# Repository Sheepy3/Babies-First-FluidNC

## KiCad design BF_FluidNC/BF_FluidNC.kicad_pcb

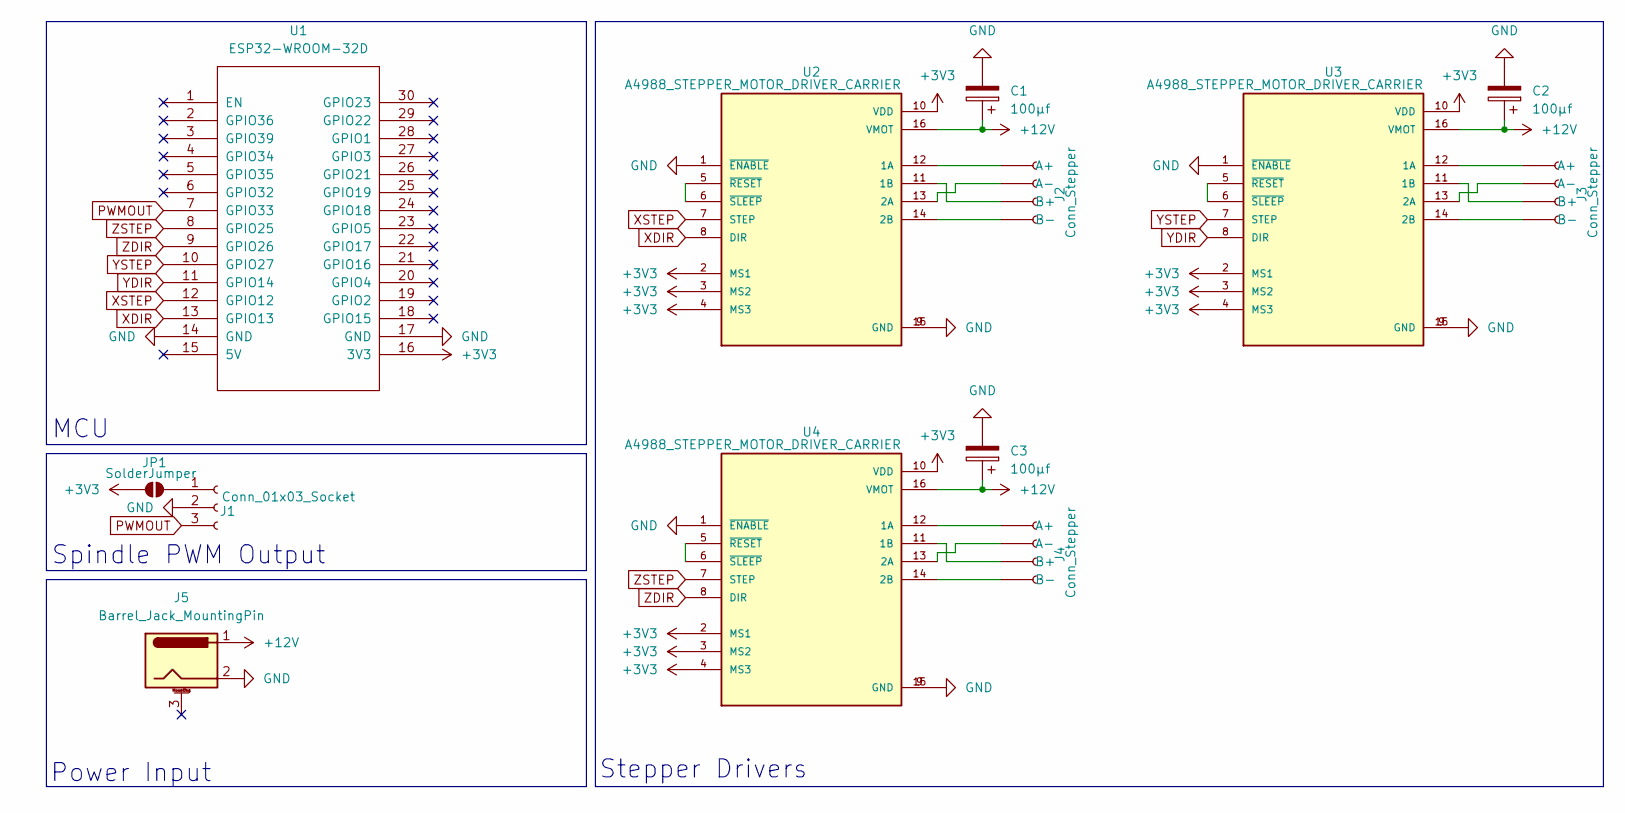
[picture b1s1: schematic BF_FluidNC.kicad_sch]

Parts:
C1, C2, C3: 100µf; CP_Radial_D5.0mm_P2.00mm
J1: Conn_01x03_Socket; PinSocket_1x03_P2.54mm_Vertical
J2, J3, J4: Conn_Stepper; PinSocket_1x04_P2.54mm_Vertical
J5: Barrel_Jack_MountingPin; BarrelJack_GCT_DCJ200-10-A_Horizontal
JP1: SolderJumper; SolderJumper-2_P1.3mm_Open_TrianglePad1.0x1.5mm
U1: ESP32-WROOM-32D; ESP32-WROOMD-Devboard
U2, U3, U4: A4988_STEPPER_MOTOR_DRIVER_CARRIER; MODULE_A4988_STEPPER_MOTOR_DRIVER_CARRIER

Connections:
+3V3: JP1.1 (A), U1.16 (3V3), U2.2 (MS1), U2.3 (MS2), U2.4 (MS3), U2.10 (VDD), U3.2 (MS1), U3.3 (MS2), U3.4 (MS3), U3.10 (VDD), U4.2 (MS1), U4.3 (MS2), U4.4 (MS3), U4.10 (VDD)
+12V: C1.1, C2.1, C3.1, J5.1, U2.16 (VMOT), U3.16 (VMOT), U4.16 (VMOT)
GND: C1.2, C2.2, C3.2, J1.2, J5.2, U1.14 (GND), U1.17 (GND), U2.1 (~ENABLE), U2.9 (GND), U2.15 (GND), U3.1 (~ENABLE), U3.9 (GND), U3.15 (GND), U4.1 (~ENABLE), U4.9 (GND), U4.15 (GND)
unnamed: J1.1, JP1.2 (B)
unnamed: J2.1 (A+), U2.12 (1A)
unnamed: J2.2 (A-), U2.13 (2A)
unnamed: J2.3 (B+), U2.11 (1B)
unnamed: J2.4 (B-), U2.14 (2B)
unnamed: J3.1 (A+), U3.12 (1A)
unnamed: J3.2 (A-), U3.13 (2A)
unnamed: J3.3 (B+), U3.11 (1B)
unnamed: J3.4 (B-), U3.14 (2B)
unnamed: J4.1 (A+), U4.12 (1A)
unnamed: J4.2 (A-), U4.13 (2A)
unnamed: J4.3 (B+), U4.11 (1B)
unnamed: J4.4 (B-), U4.14 (2B)
unnamed: U2.5 (~RESET), U2.6 (~SLEEP)
unnamed: U3.5 (~RESET), U3.6 (~SLEEP)
unnamed: U4.5 (~RESET), U4.6 (~SLEEP)
PWMOUT: J1.3, U1.7 (GPIO33)
XDIR: U1.13 (GPIO13), U2.8 (DIR)
XSTEP: U1.12 (GPIO12), U2.7 (STEP)
YDIR: U1.11 (GPIO14), U3.8 (DIR)
YSTEP: U1.10 (GPIO27), U3.7 (STEP)
ZDIR: U1.9 (GPIO26), U4.8 (DIR)
ZSTEP: U1.8 (GPIO25), U4.7 (STEP)

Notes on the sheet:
MCU
Stepper Drivers
Spindle PWM Output
Power Input

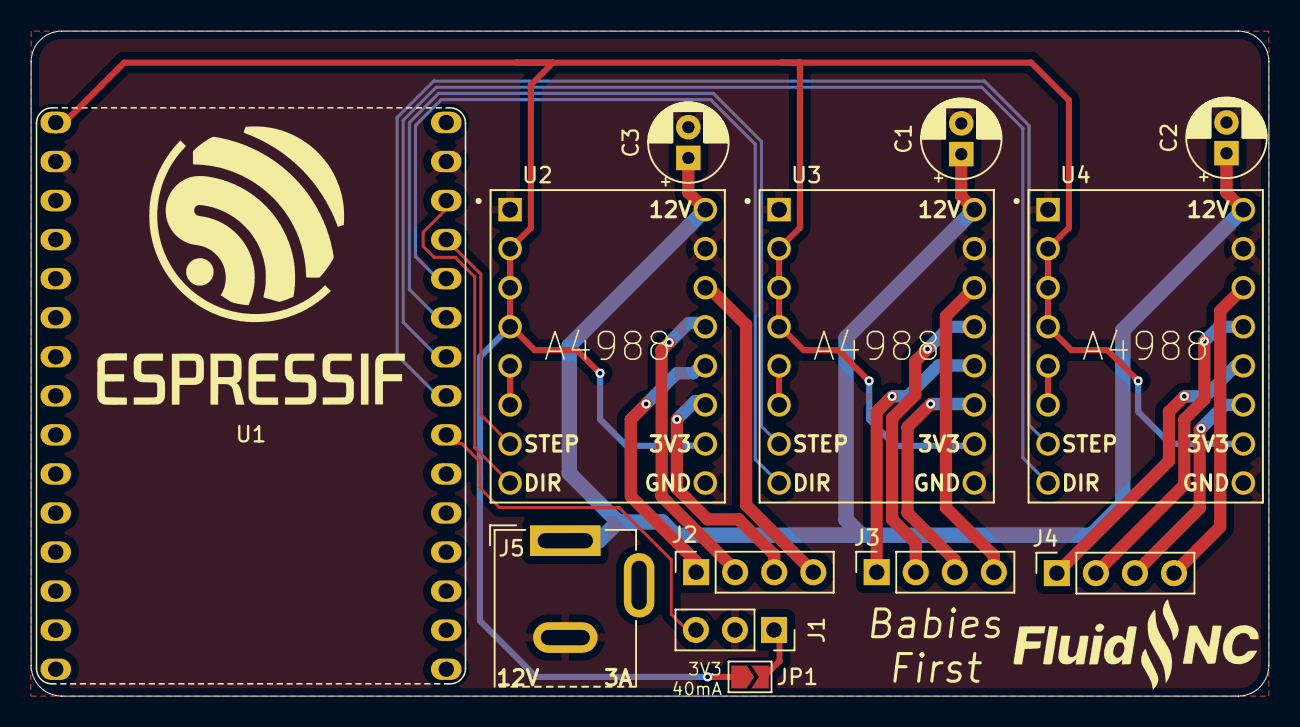
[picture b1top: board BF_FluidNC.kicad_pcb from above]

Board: 2 copper layers, 80.5 x 43.2 mm, 13 parts (0 on the bottom side), 26 nets.

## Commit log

2024-08-30 init commit
2024-09-26 updated PCB from review notes
2025-02-25 new gerbers
